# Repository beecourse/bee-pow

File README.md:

bee-pow
=======

The **pow**er supply [bee](https://github.com/beecourse) provides the voltages U_B+ = 15 V, U_B- = - 15 V and U_B2.
The value of U_B2 depends on the jumpers at JP1 and JP2 according to the following table (`--` indicates the jumper position):

  JP1  |  JP2  |          U_B2
-------|-------|------------------------
 `ooo` | `o--` | 5 V generated from U_B2
 `--o` | `--o` | 5 V generated from U3
 `o--` | `ooo` | U3

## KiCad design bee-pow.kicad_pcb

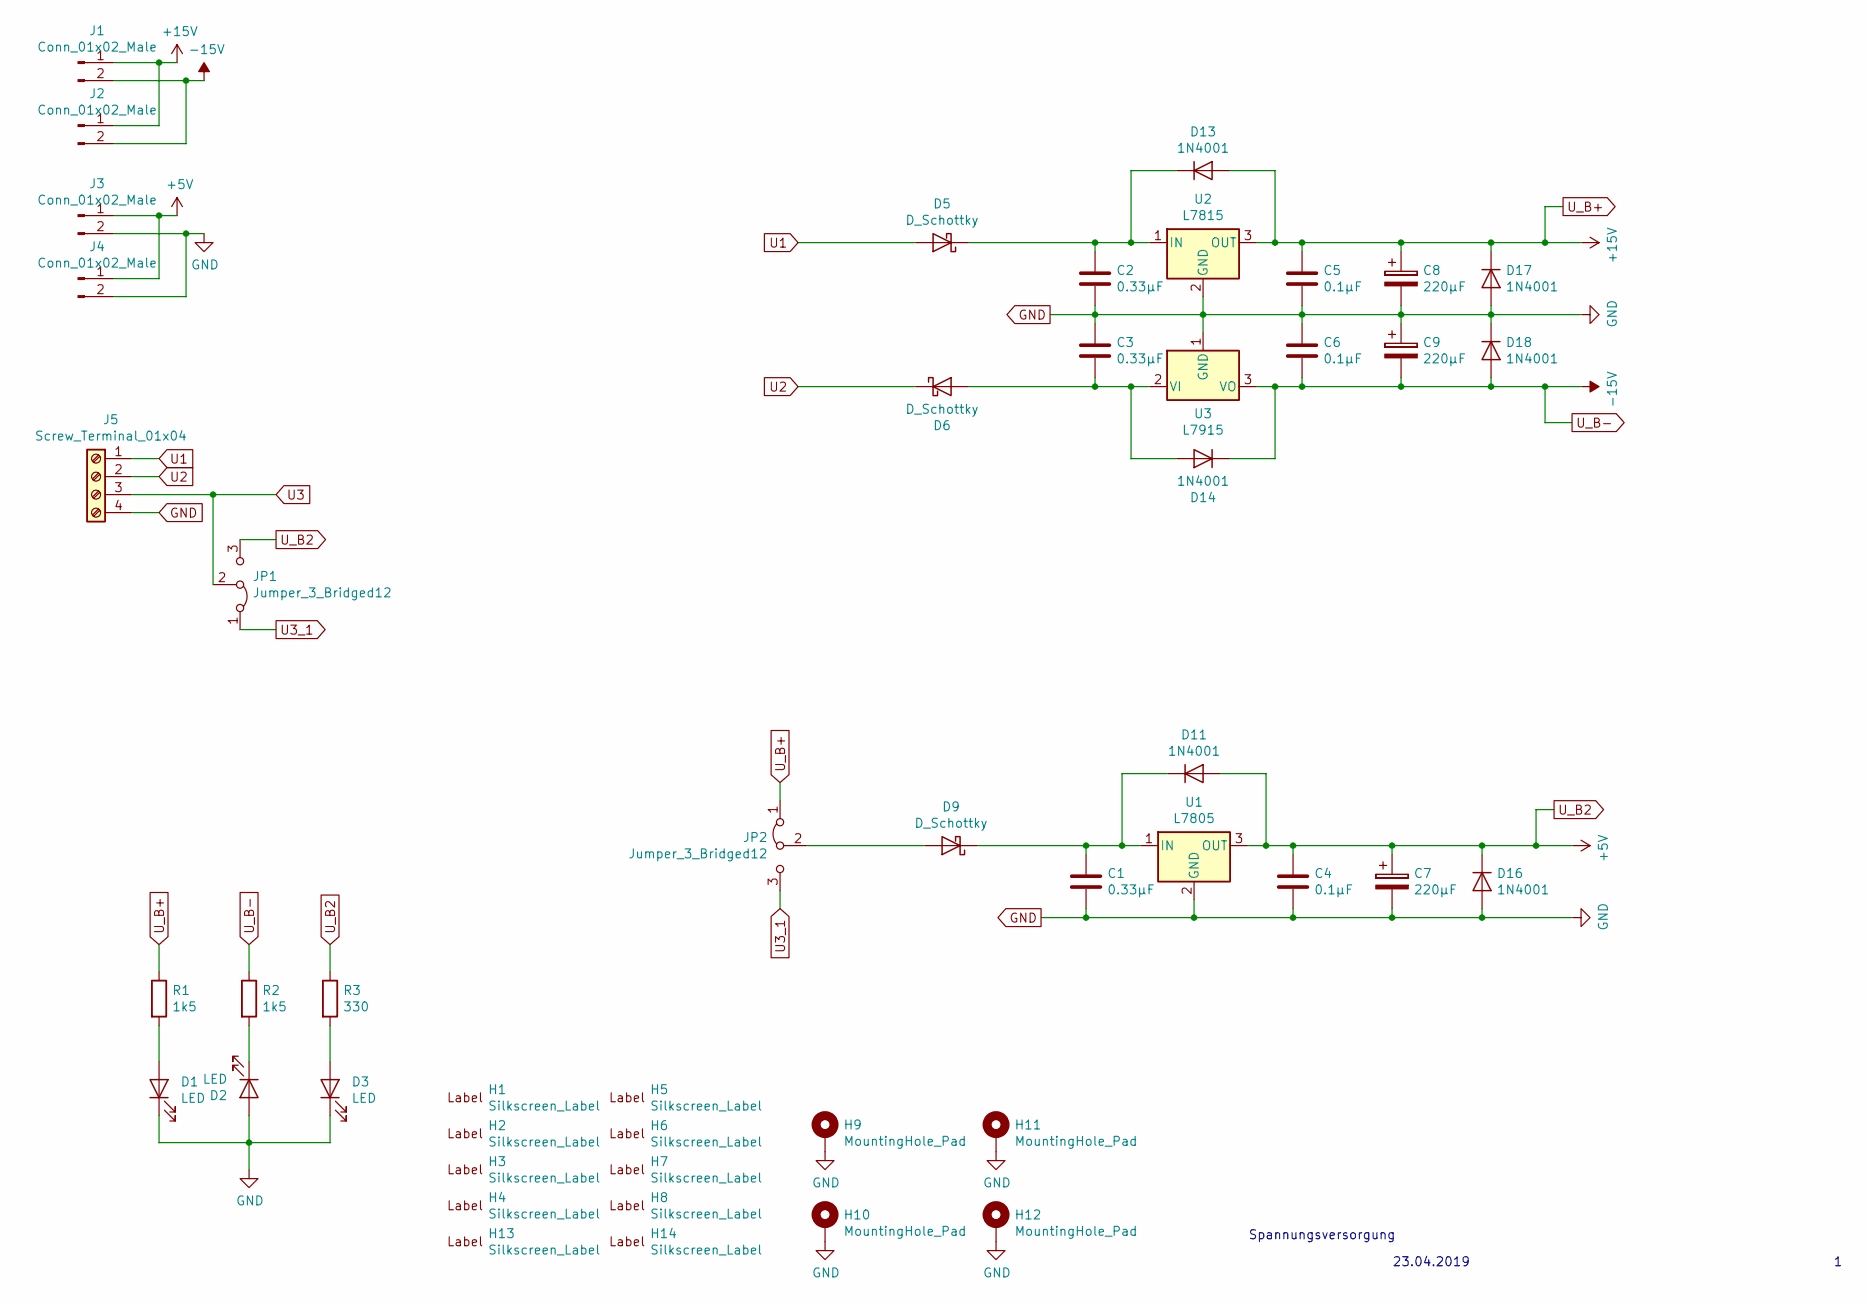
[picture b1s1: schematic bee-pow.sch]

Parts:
C1, C2, C3: 0.33µF; C_0805_2012Metric_Pad1.15x1.40mm_HandSolder
C4, C5, C6: 0.1µF; C_0805_2012Metric_Pad1.15x1.40mm_HandSolder
C7, C8, C9: 220µF; CP_Radial_D8.0mm_P2.50mm
D1, D2, D3: LED; LED_0805_2012Metric_Pad1.15x1.40mm_HandSolder
D5, D6, D9: D_Schottky; D_SMB
D11, D13, D14, D16, D17, D18: 1N4001; D_MELF_Handsoldering
H1, H2: Silkscreen_Label; Text_U_B+_Silkscreen
H3, H4: Silkscreen_Label; Text_U_B-_Silkscreen
H5, H6: Silkscreen_Label; Text_U_B2_Silkscreen
H7, H8: Silkscreen_Label; Symbol_GND_Silkscreen
H9, H10, H11, H12: MountingHole_Pad; MountingHole_3.2mm_M3_ISO7380_Pad
H13: Silkscreen_Label; EMT-Logo_5.1x2.5mm_Silkscreen
H14: Silkscreen_Label; BEE-Logo_Silkscreen_small
J1, J2, J3, J4: Conn_01x02_Male; PinHeader_1x02_P2.54mm_Vertical
J5: Screw_Terminal_01x04; TerminalBlock_bornier-4_P5.08mm
JP1, JP2: Jumper_3_Bridged12; PinHeader_1x03_P2.54mm_Vertical
R1, R2: 1k5; R_0805_2012Metric_Pad1.15x1.40mm_HandSolder
R3: 330; R_0805_2012Metric_Pad1.15x1.40mm_HandSolder
U1: L7805; TO-220-3_Vertical
U2: L7815; TO-220-3_Vertical
U3: L7915; TO-220-3_Vertical

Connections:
GND: C1.2, C2.2, C3.1, C4.2, C5.2, C6.1, C7.2, C8.2, C9.1, D1.1 (K), D2.2 (A), D3.1 (K), D16.2 (A), D17.2 (A), D18.1 (K), H9.1, H10.1, H11.1, H12.1, J3.2, J4.2, J5.4, U1.2 (GND), U2.2 (GND), U3.1 (GND)
unnamed: C1.1, D9.1 (K), D11.1 (K), U1.1 (IN)
unnamed: C2.1, D5.1 (K), D13.1 (K), U2.1 (IN)
unnamed: C3.2, D6.2 (A), D14.2 (A), U3.2 (VI)
unnamed: D1.2 (A), R1.2
unnamed: D2.1 (K), R2.2
unnamed: D3.2 (A), R3.2
unnamed: D9.2 (A), JP2.2 (C)
U1: D5.2 (A), J5.1
U2: D6.1 (K), J5.2
U3: J5.3, JP1.2 (C)
U3_1: JP1.1 (A), JP2.3 (B)
U_B2: C4.1, C7.1, D11.2 (A), D16.1 (K), J3.1, J4.1, JP1.3 (B), R3.1, U1.3 (OUT)
U_B+: C5.1, C8.1, D13.2 (A), D17.1 (K), J1.1, J2.1, JP2.1 (A), R1.1, U2.3 (OUT)
U_B-: C6.2, C9.2, D14.1 (K), D18.2 (A), J1.2, J2.2, R2.1, U3.3 (VO)

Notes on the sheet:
23.04.2019
Spannungsversorgung

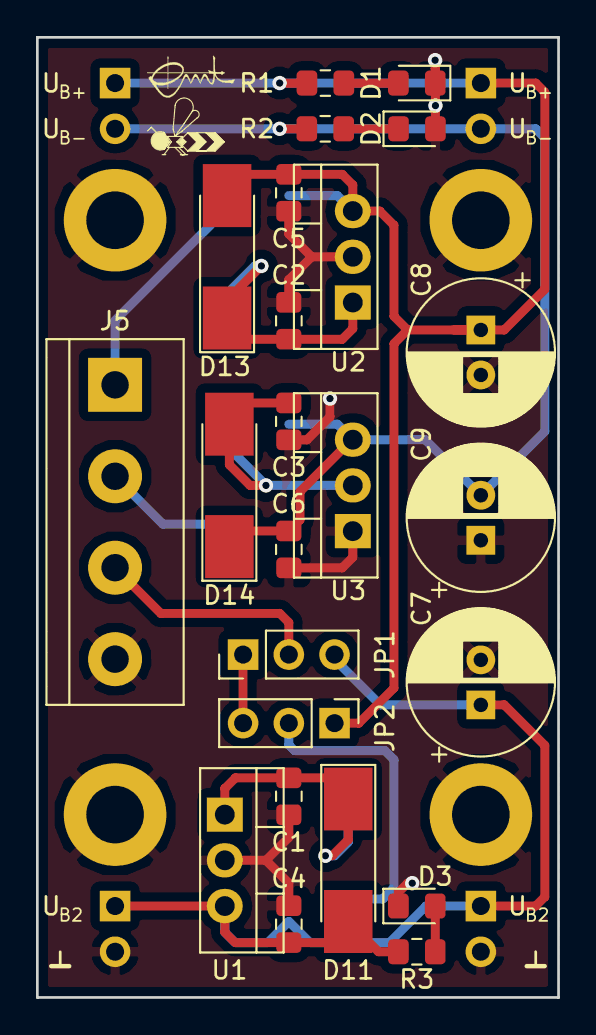
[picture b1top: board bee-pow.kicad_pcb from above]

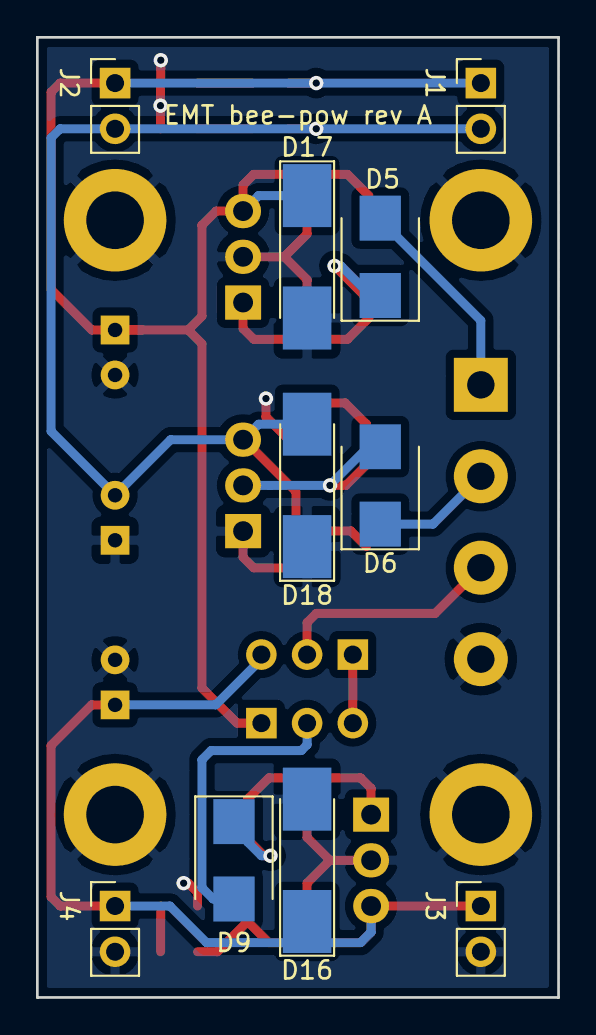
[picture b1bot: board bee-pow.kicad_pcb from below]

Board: 2 copper layers, 29.0 x 53.3 mm, 48 parts (10 on the bottom side), 15 nets.

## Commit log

2019-04-17 first commit - empty project
2019-04-17 add gitignore
2019-04-23 begin schematic
2019-04-25 schematic and layout
2019-04-29 Place refs on bottom silkscreen.
2019-04-30 Update labels and mounting holes.
2019-04-30 Update gitignore.
2019-05-02 Remove temporary file.
2019-05-03 Add ground plane.
2019-05-03 Add text and logos.
2019-05-03 DRC - add missing via, fix part distances.
2019-05-08 Add part numbers.
2019-05-22 Fix LED label position.
2020-07-01 Relabel as bee specific.
2020-07-15 Add license.
2020-07-15 Add readme.
2023-03-17 Add figure showing top view of PCB
